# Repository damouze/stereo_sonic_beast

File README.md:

# Stereo Sonic Beast

A layman's attempt at creating a stereo version of the old-fashioned parallell port DAC.

## Preface & disclaimer

Let me start by pointing out that I am not an electronic engineer. Everything I know about electronics I learned from the internet and from two electronic design courses during my university days, and nearly all of it is theoretical. I am really more of a software person who decided at one point in his not-so-distant past that it might be fun to start learning to design (digital) electronic circuits. 

That said, this is not my first KiCAD project. There have been couple before this one that I may or may not decide to publish at a later stage. However, this is the first project that I feel somewhat confident about. 

This design is bound to have some flaws, and I would love to hear about them from you. Just keep in mind that I do have a day job and that it takes precedence if I do not respond to them within a day. As a person without an actual background in electronic design I am sure I am making assumptions about components in the design that are incorrect or otherwise potentially troublesome. 

Ok, enough ranting. Let's have a look at this project.

## The Stereo Sonic Beast

A while ago, youtuber Necroware posted a [video](https://www.youtube.com/watch?v=DKLKtH_rQJU) about a recreation of the (in)famous [Covox Speech Thing](https://en.wikipedia.org/wiki/Covox_Speech_Thing) he did. For those of you who may not know: this was a device from the late eighties and early nineties that would turn your parallell printer port into an audio device. It was basically a DAC constructed of a set of resistors in a circuit that is usually called a resistor ladder. 

The design was simple, yet elegant and for its time it produced decent audio output and just about the only thing the computer it was attached to needed to do to make it output audio was to write data to the printer port at the appropiate rate. Necroware calls his recreation the "Silly Sound Bastard". It had a way of producing dual-mono sound by connecting the device's single audio channel to both output channels on the audio jack.

This made me wonder if it were possible to design a variant of this that would output actual stereo sound and decided that I would attempt it. 

What you find in this repository is one of the first iterations of this design. What it basically boils down to is that the actual audio output comes from two latches, one for each channel and that each channel has its own DAC. The input pins of the latch responsible for the left channel are enabled first, the ones for the right channel are enabled next, and so on. 

In theory, this should provide stereo capability to the original design and the only thing that the computer needs to do is to send the sample data for the left and right channel in an interleaved fashion: the octet for the left channel is sent first, the octet for the right channel is sent next, and so on.

So I present to you: The Stereo Sonic Beast.

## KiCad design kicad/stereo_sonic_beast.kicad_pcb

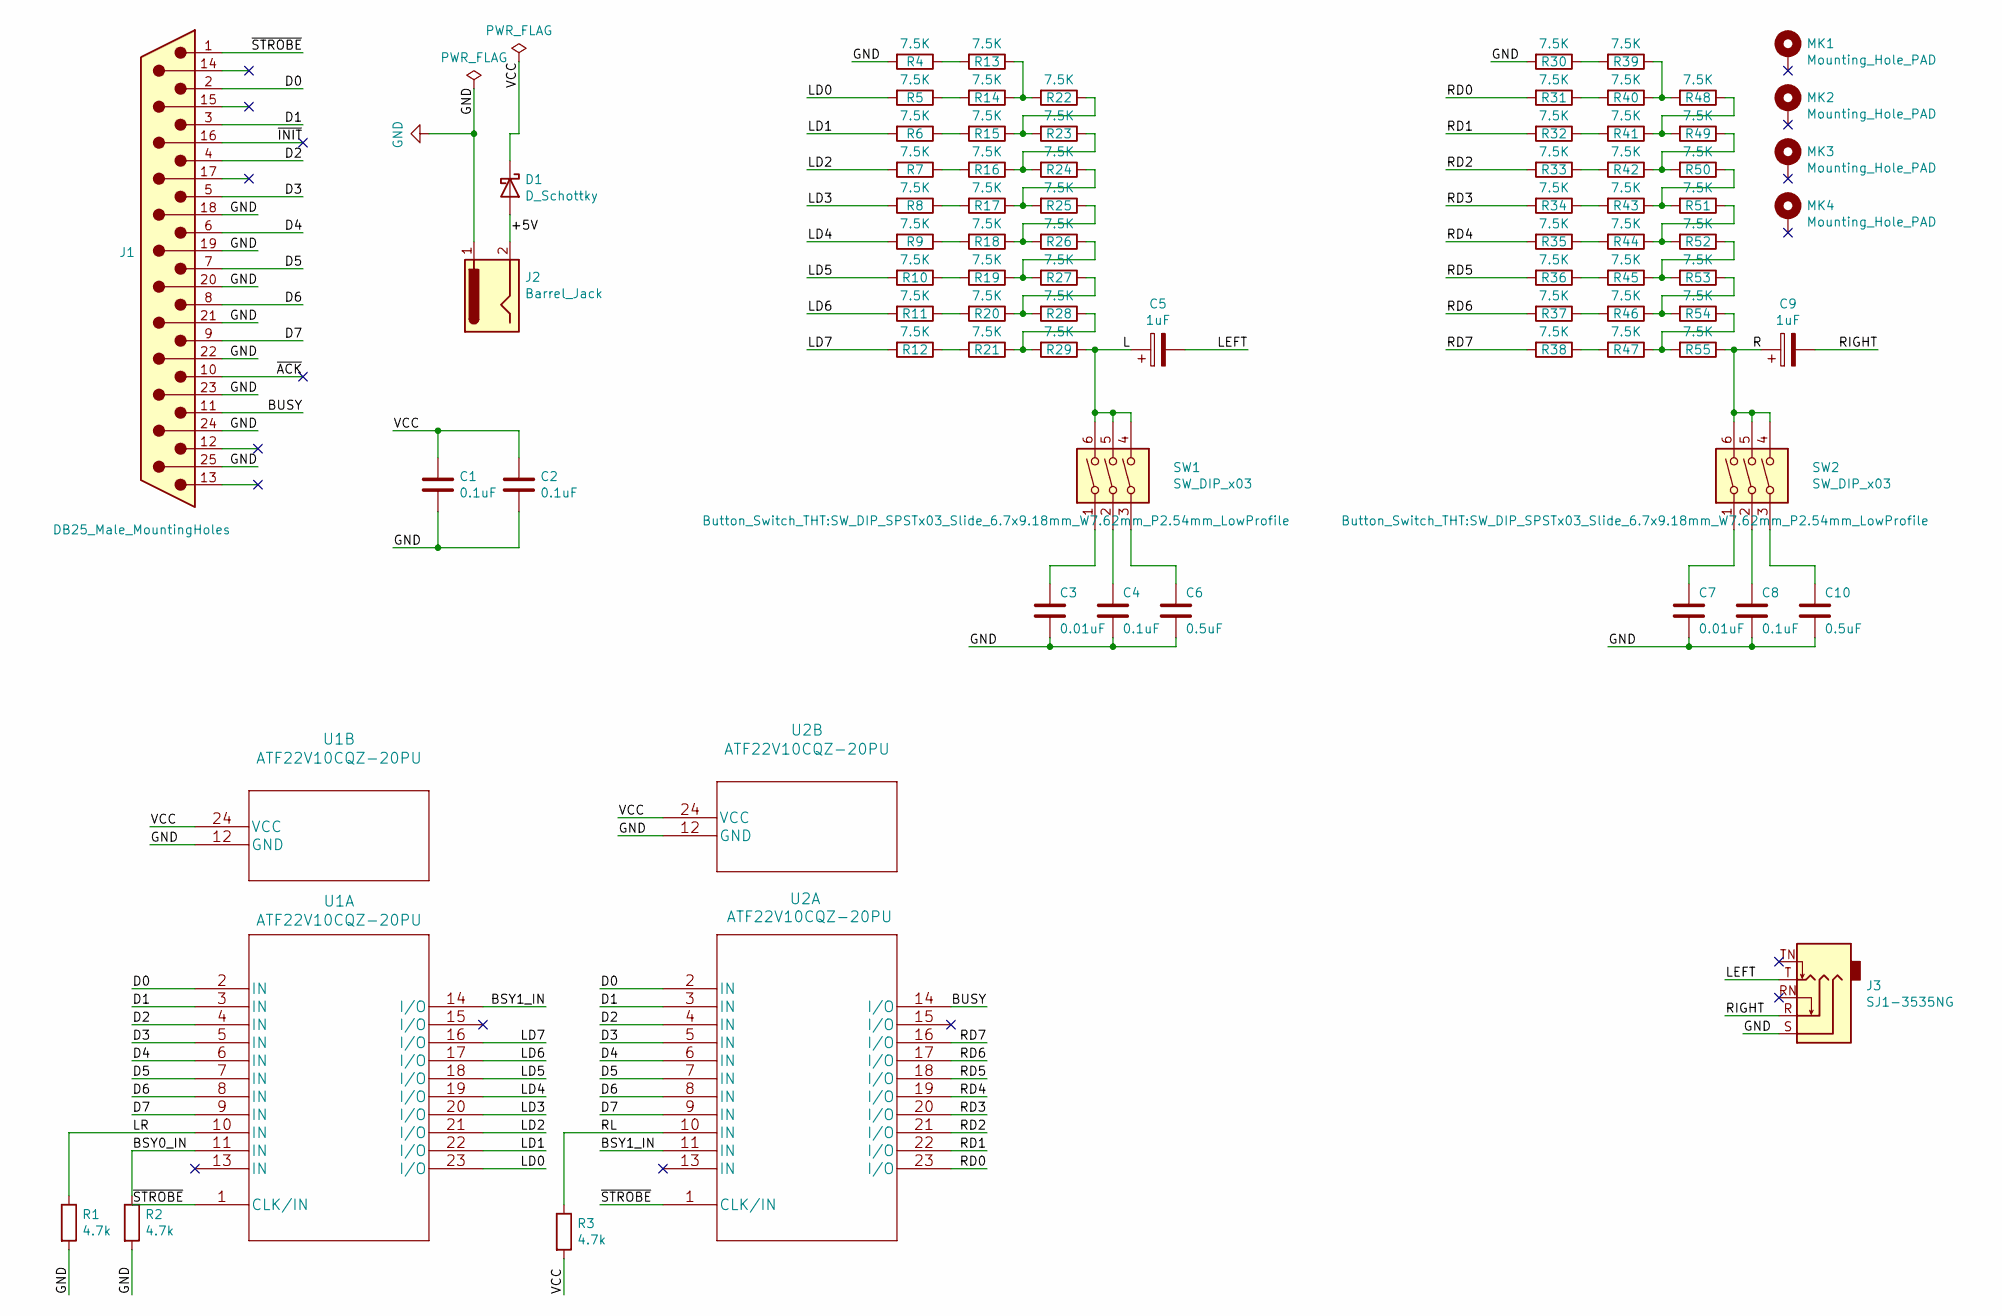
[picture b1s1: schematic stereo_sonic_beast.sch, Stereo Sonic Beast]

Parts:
C1, C2, C4, C8: 0.1uF; C_Disc_D3.0mm_W1.6mm_P2.50mm
C3, C7: 0.01uF; C_Disc_D3.0mm_W1.6mm_P2.50mm
C5, C9: 1uF; CP_Radial_D4.0mm_P1.50mm
C6, C10: 0.5uF; C_Disc_D3.0mm_W1.6mm_P2.50mm
D1: D_Schottky; D_T-1_P5.08mm_Horizontal
J1: DB25_Male_MountingHoles; DSUB-25_Male_Horizontal_P2.77x2.54mm_EdgePinOffset9.40mm
J2: Barrel_Jack; BarrelJack_CUI_PJ-063AH_Horizontal_CircularHoles
J3: SJ1-3535NG; Jack_3.5mm_CUI_SJ1-3535NG_Horizontal
MK1, MK2, MK3, MK4: Mounting_Hole_PAD; MountingHole_2.7mm
R1, R2, R3: 4.7k; R_Axial_DIN0204_L3.6mm_D1.6mm_P5.08mm_Horizontal
R4, R5, R6, R7, R8, R9, R10, R11, R12, R13, R14, R15, R16, R17, R18, R19, R20, R21, R22, R23, R24, R25, R26, R27, R28, R29, R30, R31, R32, R33, R34, R35, R36, R37, R38, R39, R40, R41, R42, R43, R44, R45, R46, R47, R48, R49, R50, R51, R52, R53, R54, R55: 7.5K; R_Axial_DIN0204_L3.6mm_D1.6mm_P5.08mm_Horizontal
SW1, SW2: SW_DIP_x03; SW_DIP_SPSTx03_Slide_6.7x9.18mm_W7.62mm_P2.54mm_LowProfile
U1, U2: ATF22V10CQZ-20PU; DIP-24_W7.62mm_Socket

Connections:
/+5V: D1.2 (A), J2.2
/BSY0_IN: R2.1, U1.11 (IN)
/BSY1_IN: U1.14 (I/O), U2.11 (IN)
/BUSY: J1.11, U2.14 (I/O)
/D0: J1.2, U1.2 (IN), U2.2 (IN)
/D1: J1.3, U1.3 (IN), U2.3 (IN)
/D2: J1.4, U1.4 (IN), U2.4 (IN)
/D3: J1.5, U1.5 (IN), U2.5 (IN)
/D4: J1.6, U1.6 (IN), U2.6 (IN)
/D5: J1.7, U1.7 (IN), U2.7 (IN)
/D6: J1.8, U1.8 (IN), U2.8 (IN)
/D7: J1.9, U1.9 (IN), U2.9 (IN)
/L: C5.1, R29.1, SW1.4, SW1.5, SW1.6
/LD0: R5.2, U1.23 (I/O)
/LD1: R6.2, U1.22 (I/O)
/LD2: R7.2, U1.21 (I/O)
/LD3: R8.2, U1.20 (I/O)
/LD4: R9.2, U1.19 (I/O)
/LD5: R10.2, U1.18 (I/O)
/LD6: R11.2, U1.17 (I/O)
/LD7: R12.2, U1.16 (I/O)
/LEFT: C5.2, J3.T
/LR: R1.1, U1.10 (IN)
/R: C9.1, R55.1, SW2.4, SW2.5, SW2.6
/RD0: R31.2, U2.23 (I/O)
/RD1: R32.2, U2.22 (I/O)
/RD2: R33.2, U2.21 (I/O)
/RD3: R34.2, U2.20 (I/O)
/RD4: R35.2, U2.19 (I/O)
/RD5: R36.2, U2.18 (I/O)
/RD6: R37.2, U2.17 (I/O)
/RD7: R38.2, U2.16 (I/O)
/RIGHT: C9.2, J3.R
/RL: R3.1, U2.10 (IN)
/VCC: C1.1, C2.1, D1.1 (K), R3.2, U1.24 (VCC), U2.24 (VCC)
/~STROBE: J1.1, U1.1 (CLK/IN), U2.1 (CLK/IN)
GND: C1.2, C2.2, C3.2, C4.2, C6.2, C7.2, C8.2, C10.2, J1.18, J1.19, J1.20, J1.21, J1.22, J1.23, J1.24, J1.25, J2.1, J3.S, R1.2, R2.2, R4.2, R30.2, U1.12 (GND), U2.12 (GND)
unnamed: C3.1, SW1.1
unnamed: C4.1, SW1.2
unnamed: C6.1, SW1.3
unnamed: C7.1, SW2.1
unnamed: C8.1, SW2.2
unnamed: C10.1, SW2.3
unnamed: R10.1, R19.2
unnamed: R11.1, R20.2
unnamed: R12.1, R21.2
unnamed: R13.1, R14.1, R22.2
unnamed: R4.1, R13.2
unnamed: R5.1, R14.2
unnamed: R15.1, R22.1, R23.2
unnamed: R6.1, R15.2
unnamed: R16.1, R23.1, R24.2
unnamed: R7.1, R16.2
unnamed: R17.1, R24.1, R25.2
unnamed: R8.1, R17.2
unnamed: R18.1, R25.1, R26.2
unnamed: R9.1, R18.2
unnamed: R19.1, R26.1, R27.2
unnamed: R20.1, R27.1, R28.2
unnamed: R21.1, R28.1, R29.2
unnamed: R30.1, R39.2
unnamed: R31.1, R40.2
unnamed: R32.1, R41.2
unnamed: R33.1, R42.2
unnamed: R34.1, R43.2
unnamed: R35.1, R44.2
unnamed: R36.1, R45.2
unnamed: R37.1, R46.2
unnamed: R38.1, R47.2
unnamed: R39.1, R40.1, R48.2
unnamed: R41.1, R48.1, R49.2
unnamed: R42.1, R49.1, R50.2
unnamed: R43.1, R50.1, R51.2
unnamed: R44.1, R51.1, R52.2
unnamed: R45.1, R52.1, R53.2
unnamed: R46.1, R53.1, R54.2
unnamed: R47.1, R54.1, R55.2

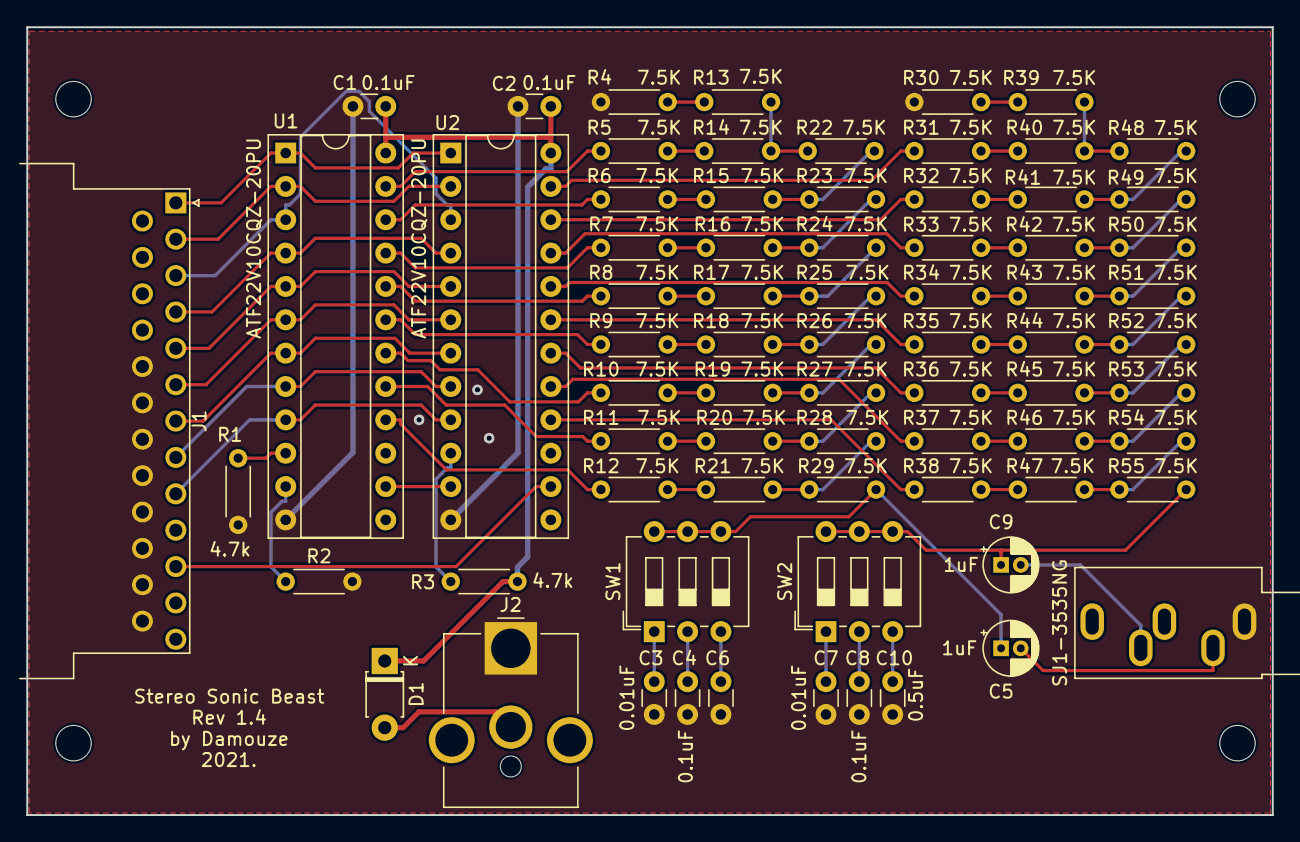
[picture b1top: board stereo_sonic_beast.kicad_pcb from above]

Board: 2 copper layers, 94.9 x 60.0 mm, 77 parts (0 on the bottom side), 77 nets.

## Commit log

2021-11-19 Added all files.
2021-11-19 PDF file for schema added.
2021-11-21 Actual information in README.md.
2021-11-21 Formatting.
2021-11-21 Still more formatting.
2021-11-21 Even more formatting.
2021-11-21 And m ore formatting....
2021-11-21 Some clarifications in the description.
